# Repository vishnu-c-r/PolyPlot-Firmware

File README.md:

# SSK Multi-Pen Plotter Firmware

A custom firmware for an ESP32-based multi-pen plotter with automatic tool changing capabilities, designed for educational tinkering labs across Kerala schools.

## 🎯 Project Overview

This project is part of a government initiative undertaken by **SSK** to establish tinkering labs in **98 schools across Kerala**. The multi-pen plotter provides students with hands-on experience in machine programming and operation, fostering practical learning in automation and digital fabrication.

### Key Features

- **🖊️ Multi-Pen Plotting**: Support for multiple pens with automatic tool changing
- **🔄 Automatic Tool Change**: M6T<X> command for seamless pen switching (X = pen number)
- **📱 Multiple User Interfaces**: Built-in UI for drawing and image import
- **🌐 Connectivity**: Serial, WiFi, and Bluetooth communication support
- **💾 Storage**: SD card support for storing drawings and configurations
- **🔦 Laser Pointer**: Integrated laser pointer for positioning and alignment
- **⌨️ Input Control**: Keypad interface via daughter board
- **🎛️ Web Configuration**: FluidNC web installer for easy machine setup

## 🏗️ Hardware

- **Microcontroller**: ESP32 with custom PCB design
- **Motion Control**: Stepper motor drivers
- **Tool System**: Automatic pen changing mechanism
- **Storage**: SD card module
- **Interface**: Keypad daughter board
- **Positioning Aid**: Laser pointer module
- **Connectivity**: WiFi, Bluetooth, Serial communication

## 🚀 Installation

### Prerequisites

- FluidNC Web Installer
- Git (for cloning the repository)

### Setup Process

1. **Clone the Repository**

   ```bash
   https://github.com/vishnu-c-r/PolyPlot-Firmware.git
   cd PolyPlot-Firmware
   ```

2. **Install Firmware**
   - flash the firmware using platformio or arduino

3. **Configure Machine**
   - Use the FluidNC web installer to set the machine configuration
   - Upload your specific plotter parameters and tool definitions

## 📖 Usage

### Basic Operations

#### Tool Changing

Use the M6T command to change tools automatically:

```gcode
M6T1  ; Change to pen 1
M6T2  ; Change to pen 2
M6T3  ; Change to pen 3
```

#### Drawing Operations

- Import SVG images through the built-in UI
- Use the web interface for real-time control
- Connect via serial, WiFi, or Bluetooth for remote operation

### User Interface Options

1. **Built-in UI**: Direct machine interface for drawing and image import
2. **Web Interface**: Browser-based control panel
3. **Serial Terminal**: Command-line interface for advanced users
4. **Mobile Apps**: Bluetooth connectivity for mobile control

## 🔧 Configuration

The machine configuration is handled through the FluidNC web installer. Key parameters include:

- Stepper motor settings
- Tool change positions and sequences
- Communication interface settings
- SD card and storage options
- UI preferences and display settings

## 🎓 Educational Applications

Perfect for:

- **STEM Education**: Hands-on programming and automation learning
- **Art & Design**: Digital art creation and physical plotting
- **Engineering Concepts**: Understanding CNC principles and G-code
- **Problem Solving**: Troubleshooting and optimization exercises

## 🔄 Version History

### Current Version

- ✅ Automatic tool changing with M6T<X> command
- ✅ Multiple UI options with built-in drawing interface
- ✅ Enhanced connectivity (Serial, WiFi, Bluetooth)
- ✅ Improved SD card handling
- ✅ Laser pointer integration
- ✅ Keypad control interface

### Previous Versions

- Basic pen plotting functionality
- Single tool operation
- Limited UI

## 🛠️ Technical Details

### Based on FluidNC

This firmware is a modified version of [FluidNC by bdring](https://github.com/bdring/FluidNC), customized specifically for multi-pen plotting applications with automatic tool changing capabilities.

### Communication Protocols

- **Serial**: USB/UART communication
- **WiFi**: Wireless network connectivity
- **Bluetooth**: Mobile device pairing

### Supported G-code Commands

- Standard FluidNC G-code set
- Custom M6T<X> tool change commands
- Extended plotting-specific commands

## 🤝 Contributing

This project is part of the SSK initiative for educational tinkering labs. Contributions that enhance the educational value and machine functionality are welcome.

## 🙏 Acknowledgments

- **FluidNC Project**: [bdring/FluidNC](https://github.com/bdring/FluidNC) for the base firmware
- **Students and Educators**: Who will use and improve this system
- **FabLab Kerala MTM team**: for building the project from ground up

---

*Empowering the next generation of makers and engineers through hands-on learning experiences.*

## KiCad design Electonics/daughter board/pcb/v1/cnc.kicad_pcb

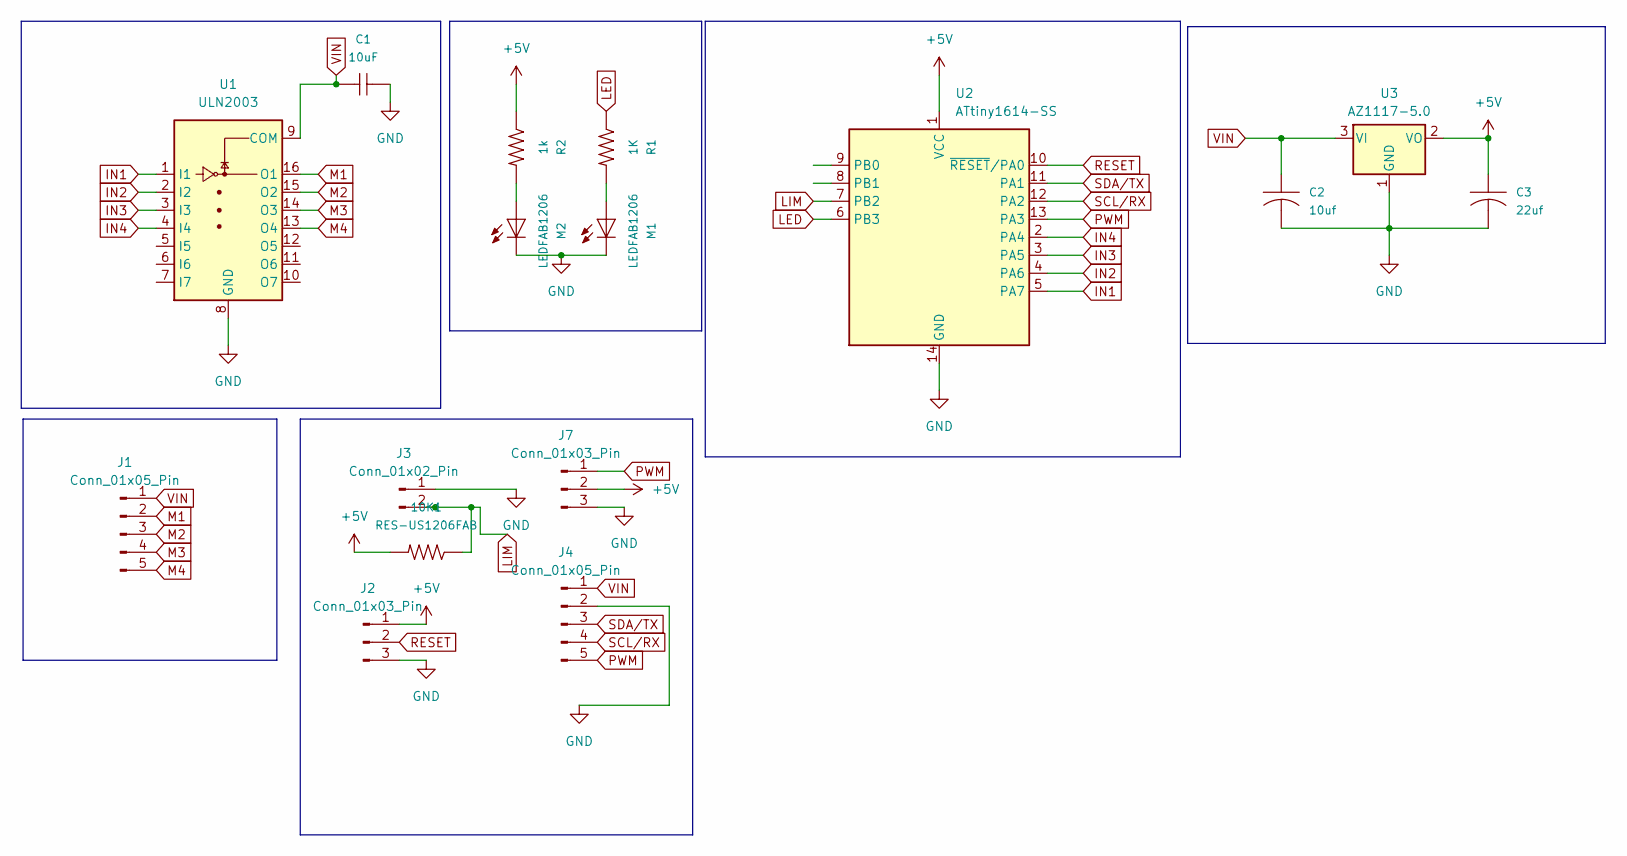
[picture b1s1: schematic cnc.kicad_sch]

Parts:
10K1: RES-US1206FAB; fab-R1206FAB
C1: 10uF; fab-C1206
C2: 10uf; fab-C1206
C3: 22uf; fab-C1206
J1: Conn_01x05_Pin; JST_XA_B05B-XASK-1_1x05_P2.50mm_Vertical
J2: Conn_01x03_Pin; Harwin_M20-89003xx_1x03_P2.54mm_Horizontal
J3: Conn_01x02_Pin; JST_XA_B02B-XASK-1_1x02_P2.50mm_Vertical
J4: Conn_01x05_Pin; JST_EH_B5B-EH-A_1x05_P2.50mm_Vertical
J7: Conn_01x03_Pin; JST_EH_B3B-EH-A_1x03_P2.50mm_Vertical
M1, M2: LEDFAB1206; fab-LED1206FAB
R1: 1K; fab-R1206FAB
R2: 1k; fab-R1206FAB
U1: ULN2003; SOIC-16_3.9x9.9mm_P1.27mm
U2: ATtiny1614-SS; SOIC-14_3.9x8.7mm_P1.27mm
U3: AZ1117-5.0; fab-SOT223

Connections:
+5V: 10K1.2, C3.1, J2.1, J7.2, R2.1, U2.1 (VCC), U3.2 (VO)
GND: C1.2, C2.2, C3.2, J2.3, J3.1, J4.2, J7.3, M1.2 (C), M2.2 (C), U1.8 (GND), U2.14 (GND), U3.1 (GND)
IN1: U1.1 (I1), U2.5 (PA7)
IN2: U1.2 (I2), U2.4 (PA6)
IN3: U1.3 (I3), U2.3 (PA5)
IN4: U1.4 (I4), U2.2 (PA4)
LED: R1.1, U2.6 (PB3)
LIM: 10K1.1, J3.2, U2.7 (PB2)
M1: J1.2, U1.16 (O1)
M2: J1.3, U1.15 (O2)
M3: J1.4, U1.14 (O3)
M4: J1.5, U1.13 (O4)
unnamed: M1.1 (A), R1.2
unnamed: M2.1 (A), R2.2
PWM: J4.5, J7.1, U2.13 (PA3)
RESET: J2.2, U2.10 (~RESET/PA0)
SCL/RX: J4.4, U2.12 (PA2)
SDA/TX: J4.3, U2.11 (PA1)
VIN: C1.1, C2.1, J1.1, J4.1, U1.9 (COM), U3.3 (VI)

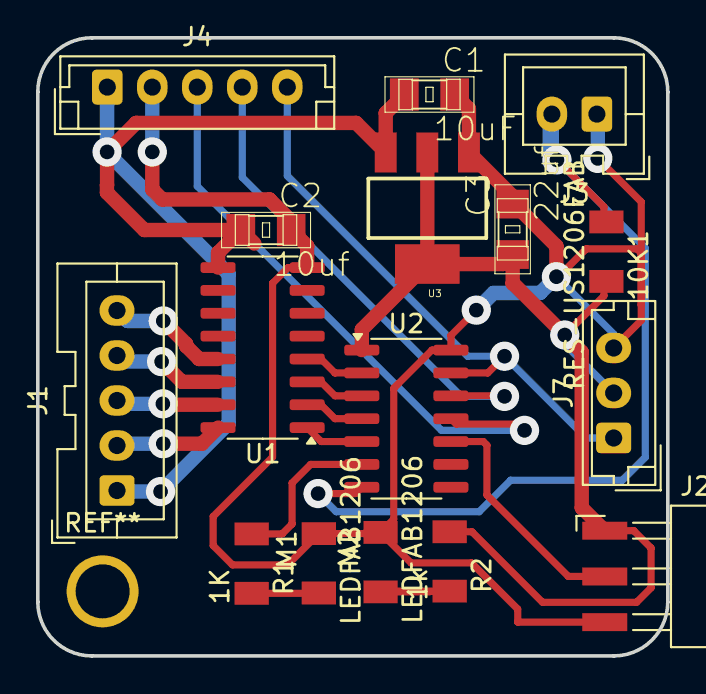
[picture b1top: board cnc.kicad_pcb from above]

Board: 2 copper layers, 35.0 x 34.3 mm, 16 parts (0 on the bottom side), 19 nets.

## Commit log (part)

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2024-06-07 test
2024-06-07 electronics
2024-06-07 Mini plotter added as directory
2024-06-07 added anand directory
2024-06-07 folder created
2024-06-07 edited md file
2024-06-10 added arduino code for mini plotter
2024-06-10 platformio
2024-06-10 okey bey
2024-06-10 changed base board as Adafruit trinket M0
2024-06-12 structured plotter
2024-06-12 structured codes
2024-06-13 new plotter
2024-06-13 new structure
2024-06-13 deleted some
2024-06-13 restructured
2024-06-27 nothing
2024-06-27 grbl stipped
2024-06-27 dir GRBL
2024-07-15 Add new directory
2024-07-15 pushed
2024-07-15 Add new file
2024-07-15 moved to folder
2024-07-15 v2 of code for daughter board
2024-07-15 pcb file
2024-07-17 tweaked for perfection
2024-07-18 grbl stripped
2024-07-24 fluid
2024-07-25 fluidnc
2024-07-25 added penmodule m code and tested
2024-07-26 added g code for pen module
2024-07-27 this is from abin
2024-07-27 deleted
2024-07-27 added changes to gcode.h and .cpp
2024-07-27 new web
2024-08-05 fully working
2024-08-05 working
2024-08-07 currently wokring firmware along with the config
2024-08-22 V1 final
2024-10-03 push
2024-10-03 firmware current
2024-10-06 Normalize line endings
2024-10-09 stripped version
2024-10-14 minor edits
2024-11-11 added motor files
2024-11-23 added code for Hbot and pen picking Motion
2024-12-08 update with LaserPointer
2025-01-04 ui working
2025-01-23 implemented ATC , and webserver fixed
2025-01-23 config file of current machine
2025-01-23 organised files and folders
2025-02-01 webserver
2025-02-01 Revert "organised files and folders"
    This reverts commit 493e1c48fdc5373c085a7cdcd7beac99bd77c3f9
2025-02-01 Revert "commit"
    This reverts commit 3266c7822957c9566c56776692b6dcca4d52b873
2025-02-01 reordered files
2025-02-03 Implement WebSocket ping-pong mechanism with timeout handling and debug logging
2025-02-03 Update pen management and configuration: adjust MAX_PENS, implement pen state restoration on failure, and integrate ToolConfig for pen locations.
2025-02-04 Add header and implementation files for alarm and error handling, and LED configuration for the keypad
2025-02-04 Add features documentation for JSON configuration, dual soft limits, safety features, manual calibration, state management, WebSocket stability, and pending implementations
2025-02-04 Add pen change tracking and configuration support, extend travel limits for pen changes, and refactor pen management
2025-02-05 Refactor WebSocket ping handling: remove ping/pong methods, adjust timeout constants, and improve zValue parsing in PenConfig
2025-02-06 Update Protocol handling and configuration: change CancelJobEvent to ArgEvent, add ToolConfig includes, and adjust PenConfig path
2025-02-09 Refactor job cancellation handling: replace CancelJobEvent with cancelJobEvent, update related command processing, and clean up unused references
2025-02-10 Refactor LED and button configuration: streamline pin definitions, reorganize timing constants, and enhance animation settings
2025-02-12 cancle job
2025-02-17 Refactor LED configuration and GrblParserC: reduce wait time to 5 seconds, fix interp function, and enhance animation timing constants for smoother transitions
2025-02-18 Refactor pin definitions and state management: change macros to static constants, reorganize state enums, and enhance function prototypes for better clarity and maintainability
2025-02-19 Add pen state and tool configuration files; refactor Protocol (enabled motors all time) and ToolConfig for improved loading and motor control
2025-02-25 Enhance WiFi fallback handling, add FeedRate to PenConfig, update config path, and improve CORS header support
2025-02-28 Add realtime command handling and refactor main header for improved clarity and maintainability improved the animations for the machine
2025-02-28 Rename FeedRate to feedRate in PenConfig
2025-04-08 Add pen configuration and update version handling
    - added the penconfig.json
    - Updated `git-version.py` to provide default version information when git is not available, ensuring a more robust versioning system.
    - Modified `WebServer.h` to include a static method for handling pen change mode.
    - Enhanced `WebSettings.cpp` to improve firmware version reporting with clearer comments.
2025-04-09 edited pen change to have multiple feedrates for a more controlled motion
2025-04-19 Implement laser offset handling with M150/M151 commands and added seperate rate for pen change
2025-04-30 Update tool configuration with new coordinates
2025-04-30 Refine feed rate handling for pen operations and introduce use_exact_feedrate flag
2025-05-05 Add support for dry run G-code validation
2025-05-15 fixed keypad timing , Reporting error and fixed whitespaces
2025-06-11 Implement job status checks and block WebSocket connections during active jobs
2025-06-25 Fix null pointer dereference in WebClient::detachWS and destructor
2025-06-30 Add program flow diagram for keypad
2025-06-30 Adjust feed rates and target positions for pen operations in GCode and MotionControl
2025-07-03 Add work area limits configuration and commands
    - Implement M160 and M161 GCode commands to enable and disable work area limits.
    - Introduce WorkArea class in MachineConfig for managing work area settings.
    - Update limits calculations to respect work area limits during operations.
    - Add functionality to move to work area origin after homing.
    - Create a WebUI command ($COFF) to retrieve work area origin settings.
2025-07-03 Refactor logging in home function and comment out status member in WebSettings
2025-08-14 Add configuration file and enhance pen change functionality
    - Added FluidNC configuration file for Poly-plot with detailed axis settings and kinematics.
    - Updated pen change logic to allow for automatic pen dropping when switching to a non-existent pen.
    - Improved motion control by refining target position handling during pen pick and drop operations.
    - Introduced new state for pen change in the system state enumeration.
    - Enhanced WebUI to include a minimal job control page for monitoring job status during active jobs.
    - Implemented job control endpoints for pause, resume, and stop functionalities.
2025-08-18 Fix WebSocket ping/pong handling to prevent disconnections during long jobs
2025-09-05 Implement Tool Calibration Feature
    - Added ToolCalibration namespace with functions to manage tool calibration.
    - Introduced startCalibration() to initiate the calibration process for X and Y axes.
    - Implemented onLimit() to handle limit pin trips during calibration.
    - Added setToolZ() to update tool Z position after calibration.
    - Updated GCode handling to support new M155 command for tool calibration.
    - Modified existing files to integrate tool calibration functionality, including state management and reporting.
2025-09-08 Checkpoint from VS Code for coding agent session
2025-09-11 update button
2025-09-11 feat: Add Work Area Calibration functionality and enhance Tool Calibration configurability
    - Introduced Work Area Calibration states and logic in Types.h and WorkAreaCalibration.cpp.
    - Updated WorkAreaCalibration.h to include new methods for starting calibration passes and handling limit events.
    - Implemented robust logging and validation for work area configuration.
    - Enhanced Tool Calibration with configurable parameters for tool racks and calibration directions.
    - Added JSON schema for tool configuration to support new features while maintaining backward compatibility.
    - Included debounce logic for limit events to improve measurement accuracy.
2025-09-29 UI: display ETA (with source & confidence) on minimal jobcontrol page
2025-11-14 Update README for clarity and correctness
2025-11-14 changed config for dlc32
2025-11-14 change config for dlc32
2025-11-26 added machine files (ui and spiffs files)
2025-12-01 Remove MAJOR_CHANGES_NOTION.md, add FIRMWARE_MODIFICATIONS.md and Configuration_Overview.md for comprehensive documentation on FluidNC firmware modifications and configuration system. beiiii
2025-12-17 Update repository URL and directory name in README
2026-01-05 Fix critical ATC logic error and WebServer memory leak
    - MotionControl.cpp:
    - Replaced static `current_loaded_pen` variable with persistent state from `ToolConfig` to prevent state desync on restart.
    - Fixed flawed boolean logic `(current_loaded_pen == nextPen == 0)` which evaluated to `true` when `nextPen` was 0 due to operator precedence. Replaced with explicit `current_loaded_pen > 0 && nextPe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
    - WebServer.cpp:
    - Fixed memory leak in `uploadStart` by deleting existing `_uploadFile` pointer before reallocation.
2026-01-05 Fix critical ATC logic, calibration direction, and memory leak
    - MotionControl.cpp: Fix ATC logic to check persistent state and correct boolean condition.
    - ToolCalibration.cpp: Fix hardcoded positive move direction. Now detects direction from ToolConfig or Homing settings. Corrects coordinate math.
    - WebServer.cpp: Fix memory leak in uploadStart.
2026-01-05 Fix critical ATC logic, calibration direction, and web server leak
    - MotionControl.cpp: Fix ATC logic to check persistent state and correct boolean condition.
    - ToolCalibration.cpp: Fix hardcoded positive move direction. Now detects direction from ToolConfig or Homing settings (defaults to searching away from home for tool banks). Corrects coordinate math.
    - WebServer.cpp: Fix memory leak in uploadStart.
